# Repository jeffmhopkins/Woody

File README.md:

# Woody

A custom electronic woodwind instrument: a wooden body with mechanical key
switches, breath and motion sensing, driving control voltage into a Eurorack
system.

This is the second iteration of the
[Open Woodwind Project](https://github.com/jeffmhopkins/Open-Woodwind-Project)
(2021), rebuilt from scratch with modern components. The previous version was a
Teensy 3.2 with capacitive touch keys and an onboard synthesizer. This one keeps
almost none of that: mechanical switches instead of capacitive pads, an ESP32-S3
instead of a Teensy, CV output instead of an onboard synth engine.

**Status: Phase 0.** Design decisions are being recorded; no hardware has been
built. Switches and keycaps are purchased. See [ROADMAP.md](ROADMAP.md).

## What it is

The project splits into two physical deliverables that meet over a single cable:

| | **Controller** | **Interface module** |
|---|---|---|
| Form | Laminated wood/aluminium/acrylic body | 10HP Eurorack module |
| Contains | Keys, breath sensor, IMU, LED matrix, MCU | DAC, analog scaling, jacks, knobs |
| Domain | Digital | Analog, ±12V |
| Primary risk | Mechanical and ergonomic | Analog precision |

The controller carries no battery and no output jacks, and all CV **scaling,
conversion and output** happens in the module. It is **not** purely digital —
it holds the pressure sensor, a precision reference, two op-amp stages and the
analog drive onto the umbilical, which is where most of the project's analog
risk lives (ADR 0003). An earlier version of this sentence said otherwise, and
ADR 0004 records that the claim let a review finding through unchallenged.

It takes power from the rack over the umbilical and sends channel data
down the same cable as SPI. The module's analog sits inches from
the jacks it drives.

These two can be developed and tested independently, and the module can be
brought up standalone on a bench long before the instrument exists.

### Output

Six CV channels from the module:

- **Pitch** — dedicated, 1V/oct, −2V to +7V, per-unit calibrated
- **Breath** — dedicated, 0–10V, with panel knobs for gain and offset
- **Mod 1–4** — assignable; source, scale, offset, curve and slew configured
  in the instrument's configuration mode, over Wi-Fi from a phone (ADR 0015,
  *Amendment, 2026-10-04*; the firmware is deferred)

And **MIDI out** on a 3.5 mm TRS jack in the tail cap, beside the etherCON,
Type A or B by a setting (`hardware/carrier/midi-out/`).

## Design scope

**This is a tethered rack instrument.** It is powered by a Eurorack system,
patched into one, and played in front of one. That is the design case, and
decisions get made for it.

It is explicitly **not**: battery powered, wireless in play, standalone, a
MIDI controller product, or a touring instrument. (Its radio is on only in a
configuration mode, for settings and updates, which does not play.) Requirements that only make sense
away from the rack do not belong here, and past versions of these documents
drifted into arguing for some of them.

The external USB is gone (issue #37): the Matrix's own USB-C is a bench and
recovery port, reached with the lid off. The MIDI out replaces USB MIDI as
the way keys, fingering and breath response get validated in a DAW before any
analog hardware is built (milestone E5). It does not get to constrain anything.

There is no onboard synthesizer. There is no battery.

**The target rack has a generous supply and a regulated +5 V rail.** Both are
stated properties of the system this is built for, not assumptions to be
defended. Rack current budget is therefore **not** a design constraint here, and
arguments of the form "a small Eurorack PSU might not cope" do not apply.

That relief is narrower than it sounds, and worth stating precisely so nobody
re-derives the wrong caution later. What still binds:

- **Heat.** The body is oak and acrylic — insulators — and sealed. Every watt
  leaves through the aluminium plate, part of which is under the player's hands.
- **The instrument's own 5 V regulator**, which is a 1 A part at the end of a
  2 m cable, not the rack supply.
- **Fault current**, which a larger supply makes *worse*, not better.

## Licence

Three share-alike licences, one per kind of work — **GPL-3.0-only** for
firmware, **CERN-OHL-S-2.0** for hardware and mechanical design,
**CC-BY-SA-4.0** for documentation. Derivatives stay open on the same terms.

See [`LICENSE`](LICENSE) for the mapping and the reasoning, and
[ADR 0011](docs/decisions/0011-licensing.md) for why it is three rather than
one.

## Repository layout

```
docs/decisions/   Architecture decision records — the important stuff
docs/log/         Dated build log
docs/reference/   Latency budgets, fingering notes, specs
docs/research/    Component comparisons and datasheet notes
docs/review/      Cold review waves. A dated record, never corrected
datasheets/       The actual vendor PDFs, one MANIFEST.csv row each
hardware/         Schematics, split by CIRCUIT under each board:
                    <board>/<circuit>/<circuit>.md  the drawing + derivations
                                      bom.csv       fragment; generates the BOM
                                      circuit.yaml  declared dependencies
                                      notes.md      what it used to be
                  interfaces/  the three circuits that cross a board boundary
                  boards/      one KiCad project per physical board, placing the
                               circuit sheets; the KiCad sheets are the source
                               of truth (ADR 0019, docs/reference/tooling.md)
                  bom.csv      GENERATED from the fragments - do not edit
firmware/         ESP32-S3 firmware (PlatformIO)
mechanical/       Body CAD (OpenSCAD, parametric): renders, DXF cut files and
                  a design-rule report, all GENERATED by tools/cad.py and
                  fingerprinted against their sources - see mechanical/README.md
config/           figures.yaml - THE SHARED-FIGURE REGISTER, the single
                  source of truth for every value used in more than one
                  document; plus key layout and routing, as data
tools/            Host-side utilities
branding/         The Space Coast Synthesizers mark: build.py generates the
                  laser artwork (SVG/DXF), a test print and renders
CLAUDE.md         THE WORKING RULES. Read this before editing anything -
                  it is short, and every rule in it was paid for once
```

*(`docs/review/` and `datasheets/` were missing from this tree until
2026-09-21. `datasheets/` is the largest directory in the repository;
`docs/review/` holds a wave per directory — `ls -d docs/review/*/` is the
count, and there is deliberately no number in this sentence. Both were
invisible in the one file a new reader opens first. The counts that used to
sit here — "77 banked documents", "seven waves", then "nine waves" — were
each true when written and wrong within the week, which is the whole reason
this repository cites rather than
restates.)*

## Where to start reading

1. [ROADMAP.md](ROADMAP.md) — the three tracks and what "done" means for each
2. [hardware/README.md](hardware/README.md) — **how the schematics are
   organised**: one circuit per directory, what the four files in each are,
   and the two rules that will bite you. Start here before opening any
   circuit page.
3. [docs/decisions/](docs/decisions/) — every choice made so far, and why
4. [docs/reference/latency-budget.md](docs/reference/latency-budget.md) — the
   constraint that shapes most of the electrical design
5. [docs/reference/repo-maintenance.md](docs/reference/repo-maintenance.md) —
   which files are generated, which are history, what each tool owns
6. [docs/reference/tooling.md](docs/reference/tooling.md) — **installing and
   using the tools**: the body CAD (OpenSCAD) and the schematic sheets
   (KiCad 9), one setup script for both

*(Entry 2 was missing until 2026-09-21. `hardware/README.md` — the page that
explains the whole `<board>/<circuit>/` scheme the restructure exists to
create — had **zero inbound links from anywhere in the corpus**, so the tree
was navigable by `grep` and by already knowing where things were, which is
the condition the restructure was meant to end.)*

*(This file carried a second "Licensing" section here saying the licence was
"not yet decided", contradicting the "Licence" section above it, which states
the three that were chosen. ADR 0011 has read `Accepted` since it was written
and `LICENSE` has held the mapping the whole time. Deleted 2026-09-21 — the
licence is stated once, above, and nowhere else.)*

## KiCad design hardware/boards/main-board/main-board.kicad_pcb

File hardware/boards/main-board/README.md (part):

# Main board — `main-board`

The one long board at the thumb level (ADR 0017). It carries:
- the thumb switches and both thumb registers;
- the carrier's circuits: the breath sensor's reference, buffer and ADC, power
  entry, the LED drive and the LED row (ADR 0028), the service header and the
  SPI egress;
- the key chain's two ribbon headers;
- `J-UMB`, where the umbilical arrives from the etherCON's adapter (ADR 0021).

The Matrix is on the right-hand key board's rails (ADR 0021 amendment
2026-10-02) and reaches it by an IDC ribbon from that board into `J-MCU`. The board
is part of the cassette (ADR 0025): every one of its mounts stands on the one
bottom plate, and eight of them are columns up to the key boards (ADR 0022 as
amended).

> **Status (2026-11-21): laid out by hand (#48, ADR 0030), the two `J-CHAIN` headers vertical since #49; `pcb.py check` passes.**
> `main_layout.py` places every part and writes out every track and via; no router ran.
> It follows the two key boards and the Matrix carrier: both `J-CHAIN` headers stand
> straight under theirs, and `J-MCU` takes the ribbon's new pin order. The outline, the thirteen
> LEDs, the switches, the mounts and the connectors are where the body CAD puts them
> (`mechanical/export/main-board.dxf`, the `main` entries in
> `mechanical/export/pcb-geometry.echo`). `fab/` and the renders are this board's. The
> sheets are the source and pass KiCad's ERC. Every part has its footprint and bought
> part on its symbol (`Footprint`, `Manufacturer`, `MPN`, `LCSC`, `Assembly`), from
> selections whose datasheets are banked, and every machine-placed part with a polarity
> or more than two pads has its JLC rotation (`hardware/lib/jlc-rotation.csv`). The
> thumb switch positions are provisional until M2/M3, as the key boards' are.

What each circuit does, and why, is on its page:
- [`carrier.md`](../../carrier/carrier.md), the board's own page, and its
  circuits:
  - [`breath-adc`](../../carrier/breath-adc/breath-adc.md)
  - [`breath-excitation-reference`](../../carrier/breath-excitation-reference/breath-excitation-reference.md)
  - [`power-entry-instrument`](../../carrier/power-entry-instrument/power-entry-instrument.md)
  - [`service-uart`](../../carrier/service-uart/service-uart.md)
  - [`led-strip-drive`](../../carrier/led-strip-drive/led-strip-drive.md)
- The thumb clusters:
  - [`key-register`](../../cluster/key-register/key-register.md)
  - [`key-switch-network`](../../cluster/key-switch-network/key-switch-network.md)
  - [`key-marker-and-bits`](../../cluster/key-marker-and-bits/key-marker-and-bits.md)
- The interfaces whose main-board parts the root sheet draws:
  - [`key-chain-loom`](../../interfaces/key-chain-loom/key-chain-loom.md)
  - [`breath-sense-link`](../../interfaces/breath-sense-link/breath-sense-link.md)
  - [`spi-link`](../../interfaces/spi-link/spi-link.md)

## Files — what is source, what is generated

| File | What it is |
|---|---|
| `main-board.kicad_sch` (+ the circuit sheets it places) | **Source.** Every connection, and each part's identity (ADR 0019) |
| `board-netlist.yaml` | Exported from the sheets (`tools/kicad.py export hardware/boards/main-board`), with KiCad's ERC over the whole hierarchy |
| `*.sch.png`, `*.pcb-*.png` | Renders, recorded in `hardware/SHEETS.csv` |
| `fab/` | **Generated** by `tools/pcb.py render` (Gerbers, drill, placement), recorded in the ledger against the board and the sheets. Never edit it by hand: `kicad.py check` fails on a stale file, and on any file in `fab/` that no tool wrote |
| `fp-lib-table` | Registers `hardware/lib/woody.pretty` (the KS-33, `J-CHAIN`, `J-MCU`, `J-UMB`, MPXV4006DP and WS2815B-V1 footprints, and through them their 3D models) for this project |
| `sym-lib-table` | Registers `hardware/lib/woody.kicad_sym` (the WS2815B-V1's symbol) for this project |
| `main_layout.py` | **The record of the layout** (ADR 0030): every part's place and every track and via, written out by hand with the reason for each. It rewrites `main-board.kicad_pcb`. No router runs on this board |
| `main-board.kicad_pcb`, `main-board.kicad_pro` | Written by `main_layout.py`. Change the layout there and run it, so the reasons stay with the copper; `pcb.py check` holds the board to the sheets, the body CAD and `layout.yaml` |
| `layout.yaml` | The limits the board is held to (`kind: main`): the rules, the stackup, the planes, the `AGND_INST` island and its tie, the breath pair's keep-off, the net classes, keep-outs, heights, iron room, and what its silkscreen says |

The root sheet places, once per instance:
- **the six carrier circuits**;
- **`breath-sense-link`**, whose parts are all on this board;
- **the two thumb registers** (`REG-LT`, `REG-RT`);
- **one key network per thumb key**, plus one at each of the right thumb's
  two reserved spare positions (`sw+`, `sw-`);
- **one pull-up per free bit** (`FREE1`, `FREE2`).

The registers' inputs are wired as `hardware/cluster/key-marker-and-bits/allocation.yaml`
says. Its own parts are the interface circuits' main-board halves:
- from key-chain-loom: both `J-CHAIN` headers, the series resistors, the
  SER terminator, the two beads and the clamp;
- from spi-link: `J-UMB`.

On this board the chain's return is `PWR_GND` and its 3V3 is `DEV_3V3`
(`hardware/nets.yaml`).

`tools/kicad.py check` holds the board to three things:
- the registers' wiring against `allocation.yaml`;
- each `J-CHAIN` pin against the loom's `J-CHAIN-MAIN-<LH|RH>`;
- ERC.

## The references

Numeric, as the key boards'. The BOM row each one buys from is its `Row` field.

| References | BOM row | Sheet |
|---|---|---|
| C1 | `C-AA-ADC` | breath-adc |
| C2 | `C-ADC-BULK` | breath-adc |
| C42 | `C-ADC-VDD` | breath-adc |
| C11 | `C-BUCK-IN` | power-entry-instrument |
| C43 | `C-BUCK-OUT` | power-entry-instrument |
| C13, C14, C205, C206 | `C-DECOUPLE-165` | REG-LT, REG-RT |
| C3, C6–C8, C12, C204 | `C-DECOUPLE-CARRIER` | breath-adc, breath-excitation-reference, led-strip-drive |
| C9 | `C-FB-REF` | breath-excitation-reference |
| C40 | `C-INRUSH-GD` | power-entry-instrument |
| C39 | `C-INRUSH-GS` | power-entry-instrument |
| C15–C24 | `C-KEY` | LT1, LT2, LT3, LT4, RT1, RT2, RT3, RT4, sw+, sw- |
| C26–C38 | `C-LED` | led-strip-drive |
| C4, C5 | `C-REF-OUT` | breath-excitation-reference |
| C203 | `C-SENSOR-OUT` | breath-sense-link |
| C201 | `C-SENSOR-VS-BULK` | breath-sense-link |
| C202 | `C-SENSOR-VS-HF` | breath-sense-link |
| C10, C44 | `C-STRIP-BULK` | power-entry-instrument |
| C45–C47 | `C-STITCH-12V` | power-entry-instrument |
| C207, C208 | `C-USBOR` | power-entry-instrument (#39) |
| D21 | `D-INRUSH-RST` | power-entry-instrument |
| D8–D20 | `D-LED` | led-strip-drive |
| D1 | `D-REF-CLAMP` | breath-excitation-reference |
| D2 | `D-REVSHUNT` | power-entry-instrument |
| D5, D6 | `D-TVS-BREATH` | breath-sense-link |
| D3 | `D-TVS-PWR` | power-entry-instrument |
| FB1, FB2 | `FB-CHAIN` | root |
| FB3, FB4 | `FB-MIDI` | midi-out (#37) |
| J2 | `HDR-SERVICE` | service-uart |
| J4, J5 | `J-CHAIN` | root |
| J7 | `J-MIDI` | midi-out (#37; side entry facing the tail since #45) |
| J8 | `J-MIDI-OUT` | midi-out (#37; through the tail cap since #45, not on this board: `layout.yaml` `not_on_board:`) |
| J1 | `J-MCU` | carrier |
| J6 | `J-UMB` | root |
| L1 | `L-BUCK-IN` | power-entry-instrument |
| NT2 | `NT-AGND` | power-entry-instrument |
| NT1 | `NT-DIG` | carrier |
| Q1 | `Q-INRUSH` | power-entry-instrument |
| Q2 | `Q-USBOR` | power-entry-instrument (#39) |
| R54, R55 | `R-ADC-SER` | breath-adc |
| R47 | `R-ADC-VDD` | breath-adc |
| R5 | `R-ADCDIV-L` | breath-adc |
| R4 | `R-ADCDIV-U` | breath-adc |
| R34–R36 | `R-CHAIN-SER` | root |
| R45 | `R-CS-PULL-ADC` | breath-adc |
| R40 | `R-CS-PULL-INST` | carrier |
| R8 | `R-FB-REF` | breath-excitation-reference |
| R9 | `R-FBX-REF` | breath-excitation-reference |
| R44 | `R-HOP-SER` | root |
| R52, R53 | `R-HOP-SER` | root |
| R42 | `R-INRUSH-G` | power-entry-instrument |
| R43 | `R-INRUSH-GD` | power-entry-instrument |
| R41 | `R-INRUSH-GS` | power-entry-instrument |
| R7 | `R-ISO-REF` | breath-excitation-reference |
| R12, R14, R16, R18, R20, R22, R24, R26, R28, R30, R32, R33 | `R-KEY-PU` | LT1, LT2, LT3, LT4, RT1, RT2, RT3, RT4, sw+, sw-, FREE1, FREE2 |
| R13, R15, R17, R19, R21, R23, R25, R27, R29, R31 | `R-KEY-SER` | LT1, LT2, LT3, LT4, RT1, RT2, RT3, RT4, sw+, sw- |
| R10 | `R-LED-PD` | led-strip-drive |
| R50, R51 | `R-MIDI` | midi-out (#37) |
| R48, R49 | `R-MIDI-PU` | led-strip-drive (#37) |
| R11 | `R-LED-SER` | led-strip-drive |
| R6 | `R-REF-IN` | breath-excitation-reference |
| R38, R39 | `R-SER-BREATH-INST` | breath-sense-link |
| R37 | `R-SER-TERM` | root |
| R1–R3 | `R-SPI-SER` | carrier |
| R56 | `R-RXD-SER` | service-uart |
| R46 | `R-TXD-SER` | service-uart |
| SW1–SW10 | `SW1-n` | LT1, LT2, LT3, LT4, RT1, RT2, RT3, RT4, sw+, sw- |
| U2 | `U-ADC` | breath-adc |
| U10 | `U-BREATH` | breath-sense-link |
| U5 | `U-BUCK` | power-entry-instrument |
| U3 | `U-BUF` | breath-excitation-reference |
| U7, U8 | `U-KEYS` | REG-LT, REG-RT |
| U6 | `U-LVLSHIFT` | led-strip-drive |
| A1 | `U-MCU-RT` | carrier |
| U4 | `U-REF-BREATH` | breath-excitation-reference |
| U9, U11 | `U-TVS-CHAIN` | root |
| U12 | `U-TVS-MIDI` | midi-out (#37) |
| U1 | `U-TVS-SPI` | carrier |
| U13 | `U-USBOR` | power-entry-instrument (#39) |

## Open, and what decides each

What is still open:

| Item | Decided by |
|---|---|
| **The LED row's places** are the body CAD's (`pcb-geometry.echo` `main` `led`, *"LED row on the main board"* in `mechanical/drc.echo`): thirteen LEDs on the centreline, `D8` (LED 1, first on the data line) past the Matrix ribbon and `D9` before it, the same distance from its edge, and `D9` to `D20` at one pitch to the mouth end (`lighting.led_tail_x`, `led_ribbon_x`, `led_pitch`; ADR 0028's amendment of 2026-11-21, whose point 2 is the LED that stands level with `J5`) (`D7` / `C25` went with the removed LED); each `C-LED` in the row on the mouth side of its LED, but `D8`'s beyond `D3`, which stands in the row between them, and `D20`'s on its far side, off the breath sensor (`main_layout.py`). Reshuffled if the diffusion test moves the count. **The WS2815B-V1's chamfer marks pin 1 (NC)**; the footprint's silk triangle marks the chamfer, and JLCPCB's own footprint agrees (`hardware/lib/README.md`) | Layout; the side-light diffusion test; the first order's placement preview |
| **Passives may go on the underside** (owner, 2026-09-29). The underside faces the grounded bottom plate, `hardware.kb_spacer_l` below it, over the board's whole length since the cassette (ADR 0025). At `boards.board_clear` that leaves no room for a part (`mechanical/drc.echo` *"main board underside room over the bottom plate"*), so an underside part needs a **window cut through the bottom plate** under it, down to the oak (the second figure on that line), and must be clear of the thumb switches' housings, pins and the mounts' spacers. Through-hole tails face the plate too: the next row. The thumb switches are already underside parts | The layout; each window goes into the bottom plate's outline in the body CAD |
| **Through-hole tails under the board** (2026-10-01): every part with plated through-hole pins pokes its tails out of the underside toward the grounded bottom plate — `J-CHAIN` ×2, `J-MCU`, `J-UMB` and `U-BUCK` (`config/body.yaml`, *THE THROUGH-HOLE TAILS UNDER THE MAIN BOARD*, says which and why these). `mechanical/drc.echo` *"through-hole tails under the main board clear of the bottom plate"* tests each against what is under it, and the body model draws them for `clash.txt`. `J-CHAIN`'s and `J-MCU`'s clear the plate as supplied. The plate ends short of `J-UMB`'s tail row, and has a window to the oak under the regulator block (`HDR-SERVICE` is surface mount since 2026-10-06, owner, and needs none) (`pcb-geometry.echo` `main` `plate`). **`U-BUCK`'s pins are cut to `boards.tht_trim` below the board after soldering** — as supplied they reach the oak even through the window. `U-BUCK` stands inside the regulator block, or the window moves with it | A part moved off its window: move the block and rebuild the body CAD; a new through-hole part: add it to `tht_tails` in `mechanical/cad/woody_body.scad` |
| **The references with no clear place on the silkscreen** stay on the fabrication layer. `tools/pcb_silk.py` (#54) places every one that has a clear place within reach of its part, on a leader line where the place is not beside it; `python3 tools/pcb_silk.py hardware/boards/main-board --audit` lists the ones left, which stand in the tightest groups (the inrush corner at the tail, the far-edge rows over the key registers) | **Decided** (owner, 2026-11-22, #54): they stay off the silkscreen, on the fab layer's assembly drawing only; no part moves for a label |
| **`C203` at `U10` pin 4** (MPXV4006DP Fig. 3): pin 4 is the corner of `U10`'s own courtyard, at the mouth and far edges, so no 0805 can stand within 3 mm of it on the top face; `C203` stands at `U3`'s input, the net's other end, as before. Nearer needs an underside part and a bottom-plate window under it | Owner |
| **`J-CHAIN` ×2 and `J-MCU` (and `J-MCU-C` on the Matrix carrier, the same footprint): their pads**' ring is at JLC's absolute minimum on the sides facing a neighbour (`fab: annular_min`; pre-fab review, issue #52 F6). It stays: the hole is the one the header's drawing asks for (`datasheets/connectors/CNCTECH-3220-XX-0100-00-1.27MM-BOX-HEADER-VERTICAL.pdf`, *Recommended PCB layout*), a smaller one gives the ring a few hundredths and takes them from the post's fit, and the pitch leaves the pad no room to grow that way (`hardware/lib/README.md`, the IDC header's row). Ask JLC's review of the production file to accept the thin side | The first order |
| **The umbilical adapter** (`PCB-UMB-ADAPTER`) is a separate small board: its schematic is [`../umb-adapter/`](../umb-adapter/README.md), not laid out | With this board's layout |

What the layout holds, and where:
- **Four layers** (ADR 0017 amendment 2026-09-29), JLCPCB's stack
  `JLC04161H-7628` [ds `datasheets/fab/JLCPCB-IMPEDANCE-STACKUPS.pdf`]. Layer 2 `PWR_GND`, layer 3
  the +12 V behind `Q-INRUSH` (`INST_POS12`, `power-entry-instrument.md` §1a); the +12 V
  ahead of it and the other rails are tracks (`layout.yaml` `net_classes:`). **`AGND_INST` is an island on layer 2** round the analog block,
  its moat bridged once by `NT-AGND` (NT2) on `U-ADC`'s tail side, where its digital pins
  (5-7) cross the moat inside the tie's window (`power-entry-instrument.md` §2); since wave 3
  the island takes all of `U-ADC` and the pocket above it where `ADC_VDD`'s capacitors
  stand (#8-3). `check` fails a second tie, an island pad off the island, and any layer-1
  track crossing the moat but at the tie or as the breath pair.
- **White solder mask** both faces, black legend (`layout.yaml` `fab:`; ADR 0028).
- **Every mount plated on `PWR_GND`**, pads both faces, no other net's copper under
  its hardware (`check`); the U-bolt legs' holes unplated, the outer layers kept
  clear round their hardware.
- **The regulator block holds `U-BUCK` alone** (a rule area), against the near edge
  (`boards.tall_side`; the far edge carries the breath pair), `C-STRIP-BULK`,
  `C-BUCK-IN` and `L-BUCK-IN` beside it where their heights fit (`check_heights`).
- **`A1` (the Matrix) and the spare switches `SW9`, `SW10`** are on the sheets and
  not on this board (`layout.yaml` `not_on_board:`, reported as notes); the spare
  positions' networks are placed.
- **`NT1`** at `J-UMB` pin 8 (ADR 0018); **`U-TVS-SPI`** on the J-MCU side of
  `R-SPI-SER`, where its three channels now are.
- **The thumb switches on the underside**, where the body CAD puts them, the near
  row turned 180° (ADR 0022).
- **`U-BREATH`'s ports point to the tail**, as the body CAD and
  `breath-sense-link.md` (*Mounting*) put them, which turns its pins 1–4 (`VS`,
  `GND`, `Vout`) to the board's far edge, away from the rest of the analog block;
  the island reaches round them (`layout.yaml` `cad_parts:`, `islands:`).
- **Every part's place and every track and via are `main_layout.py`'s** (ADR 0030). Its
  header gives the floorplan and why each part stands where it does; each stage's
  function gives its lines in the order the signal runs. In outline:
  - **The analog block** is laid out along its signal from the sensor's pins outward, on
    layer 1 over the island. The ADC's chip select and 3V3 arrive on the bottom face and
    come up inside the island, so only its three SPI lines cross the island's edge,
    beside `NT-AGND`.
  - **The breath pair** (owner, 2026-10-03: *"the analog path should just be routed along
    the top"*, the far edge): the buffer's output and its `AGND` leg side by side on
    layer 4 from the buffer along the far edge to `R38` / `R39` at `J-UMB`, stepping
    inboard at 45 degrees under each far column mount. The `AGND` leg is the inboard
    line, between the signal and every key. Its reference is the `AGND_INST` strip cut
    out of layer 3 under it. Every other net's copper on that layer, and every via,
    keeps 3W off it (`layout.yaml` `pairs:` `guard:`, held by `pcb.py check`). It has no
    guard tracks: nothing else runs in that band on that layer.
  - **The LED data line stays on the top face** from the second LED to the mouth end.
    The first LED stands beyond the driver, in the row's tail-end place, so its two
    lines (`LED_DI` to it, `LED_D1` back from it) each take a lane on the bottom face
    under the driver: two vias a line. Each LED's capacitor stands in the row beside
    it, and their supply and ground pads reach the planes by vias beside them.
  - **The bottom face carries the lines that run the board's length**: the chain's
    trunk north of the LED row, the ADC's four lines and its 3V3 south of it, and each
    near-row key's line where it crosses under the row.
  - **The power paths carry no via** (#8-6): `UMBILICAL_POS12`, `BUCK_IN`, `BUCK_A_OUT`
    and `INST_5V_A` to the 5 V OR are top-face tracks from end to end. Where a power
    part meets a plane it does so by more than one via: three at `Q-INRUSH`'s drain, two
    at each bulk capacitor's pad, the buck's capacitors' returns, `L-BUCK-IN` and
    `D-TVS-PWR`. `D-REVSHUNT`'s anode is a track to `J-UMB`'s own ground pin.
  - **Ground**: every surface pad on `PWR_GND` has a via beside it, or shares one with
    the pad facing it. None stands in a pad (ADR 0030, point 5): the three clamps' middle
    pins, `U9` pin 2, `U11` pin 2 and `U1` pin 2, have theirs just off the pad, the line
    that passed there stepped clear of it.
- **Soldered ground pins meet the plane through relief spokes**, as on the key boards.
  `J-MCU`'s ground pins have one spoke each, all a 1.27 mm header leaves room for;
  `main-board.kicad_dru` lets those pins pass with one where the board's rule asks two
  (ADR 0030, Amendment of 2026-11-22). The one exception is the mounts, which join the
  plane solid: they are clamped and never soldered.
- **The clamps at their connector** (#8-9): `D-REVSHUNT` (D2) beside `J-UMB`'s pins 3 and
  6, and `D-TVS-PWR` (D3) on a top-face track from D2's pad, in the LED row on the mouth
  side of the first LED since that LED took the tail-end place; the buck's capacitors at
  the module (#8-7).
- **Soldering-iron room round the hand-soldered pads** (#34; `layout.yaml` `iron_room:`,
  held by `pcb.py check`): every other part's courtyard 2.0 mm from a thumb switch's pin
  pads on the top face, where they are soldered, and 1.5 mm from `U10`'s. This layout
  meets it everywhere, with no exception listed.
- **The planes stitched** (#8-8; owner, 2026-10-04, in the working chat: *"add 2-3 now"*):
  `C-STITCH-12V` from `INST_POS12` to `PWR_GND` at `J-MCU` (`C45`), `J-UMB` (`C46`) and the
  analog end (`C47`, on `PWR_GND` beside the island), each pad to its plane by its own via
  (`power-entry-instrument.md` §2, *Plane stitching*).

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
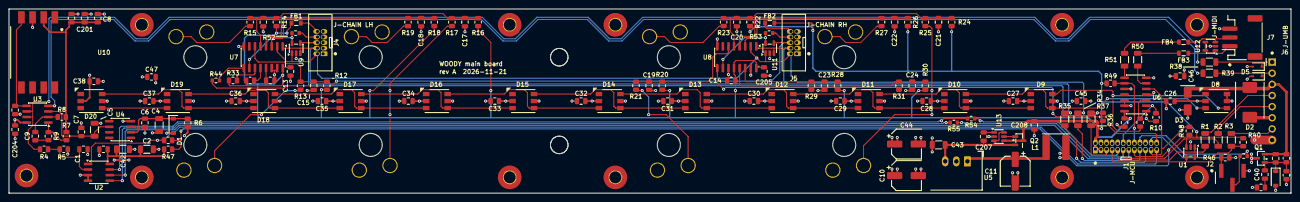
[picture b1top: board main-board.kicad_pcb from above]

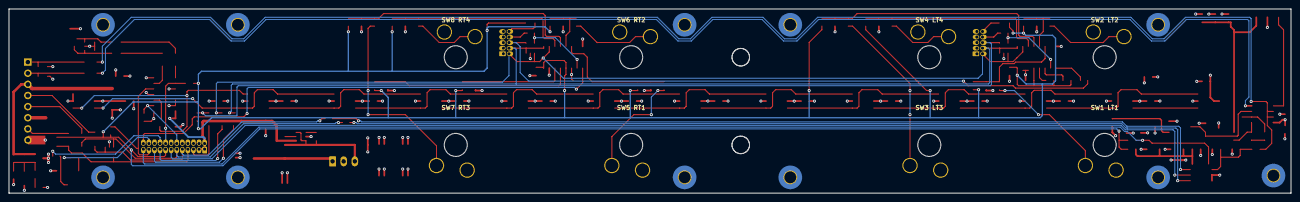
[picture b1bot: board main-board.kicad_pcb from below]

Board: 4 copper layers, 292.4 x 42.0 mm, 175 parts (8 on the bottom side), 97 nets.

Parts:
C1: 18nF C0G/NP0; C_0805_2012Metric
C2, C4, C5, C43: 10uF; C_1206_3216Metric
C3, C6, C7, C8, C12, C13, C14, C26, C27, C28, C29, C30, C31, C32, C33, C34, C35, C36, C37, C38, C204, C205, C206: 100nF; C_0805_2012Metric
C9: 1nF; C_0805_2012Metric
C10, C44: 220uF 25V; CP_Elec_6.3x7.7
C11: 100uF; CP_Elec_6.3x5.8
C15, C16, C17, C18, C19, C20, C21, C22, C23, C24: 47nF; C_0805_2012Metric
C39: 1uF 50V X7R; C_0805_2012Metric
C40: 22nF 50V X7R; C_0805_2012Metric
C42: 22uF; C_1206_3216Metric
C45, C46, C47, C207, C208: 100nF 50V X7R; C_0805_2012Metric
C201: 1uF; C_0805_2012Metric
C202: 10nF; C_0805_2012Metric
C203: 470pF; C_0805_2012Metric
D1: 15V zener; D_SOD-123
D2: SS34; D_SMC
D3: SMAJ15A; D_SMA
D5, D6: PESD12VL1BA; D_SOD-323
D8, D9, D10, D11, D12, D13, D14, D15, D16, D17, D18, D19, D20: WS2815B-V1; LED_WS2815B-V1_PLCC6_5.4x5.0mm_P1.6mm
D21: 1N4148W; D_SOD-123
FB1, FB2: Ferrite bead 600R @ 100MHz; L_0805_2012Metric
FB3, FB4: 600R@100MHz; L_0805_2012Metric
H1, H2, H3, H4, H5, H6, H7, H8: mount column; MountingHole_2.7mm_M2.5_Pad_TopBottom
H9, H10, H11: mount end; MountingHole_2.7mm_M2.5_Pad_TopBottom
J1: 2x12 1.27mm shrouded box header; IDC-Header_2x12_P1.27mm_Vertical
J2: 1x3; PinHeader_1x03_P2.54mm_Vertical_SMD_Hanxia_PZ2.54-TP-YQ
J4, J5: 10-way; IDC-Header_2x05_P1.27mm_CNCTech_3220_Vertical
J6: 8-way 2.54mm right-angle pin header; PinHeader_1x08_P2.54mm_Horizontal_Hanxia_PZ2.54-WZ
J7: S3B-PH-SM4-TB; JST_PH_S3B-PH-SM4-TB_1x03-1MP_P2.00mm_Horizontal
L1: 22uH; L_Sunlord_SWPA6028S
NT1: net tie; NetTie-2_SMD_Pad2.0mm
NT2: net tie; NetTie-2_SMD_Pad0.5mm
Q1: AO3401A; SOT-23
Q2: DMN3404L; SOT-23
R1, R2, R3: 82R 1%; R_1206_3216Metric
R4, R8, R10, R40, R45, R48, R49: 10k 1%; R_0805_2012Metric
R5: 15k 1%; R_0805_2012Metric
R6: 330R 1%; R_0805_2012Metric
R7: 37.4R 1%; R_0805_2012Metric
R9, R13, R15, R17, R19, R21, R23, R25, R27, R29, R31: 100R 1%; R_0805_2012Metric
R11: 330R; R_0805_2012Metric
R12, R14, R16, R18, R20, R22, R24, R26, R28, R30, R32, R33: 2k2 1%; R_0805_2012Metric
R34, R35, R36: 100R 1%; R_1206_3216Metric
R37: 10k; R_0805_2012Metric
R38, R39: 1k 1%; R_1206_3216Metric
R41, R42: 1M 1%; R_0805_2012Metric
R43: 22R 1%; R_0805_2012Metric
R44, R52, R53: 2k2 1%; R_0603_1608Metric
R46: 499R 1%; R_0805_2012Metric
R47: 10R 1%; R_0805_2012Metric
R50, R51: 182R 1%; R_1206_3216Metric
R54, R55: 47R 1%; R_0603_1608Metric
R56: 1k 1%; R_0603_1608Metric
SW1, SW2, SW3, SW4, SW5, SW6, SW7, SW8: KS-33; SW_Gateron_KS33_1u
U1: SP0504BAHT or equivalent 4-channel 5V array; SOT-23-5
U2: MCP3202-CI/SN; SOIC-8_3.9x4.9mm_P1.27mm
U3: OPA2197IDR; SOIC-8_3.9x4.9mm_P1.27mm
U4: REF5050IDR; SOIC-8_3.9x4.9mm_P1.27mm
U5: R-78E5.0-1.0; Converter_DCDC_RECOM_R-78E-0.5_THT
U6: 74AHCT125; SOIC-14_3.9x8.7mm_P1.27mm
U7, U8: 74HCS165; SOIC-16_3.9x9.9mm_P1.27mm
U9, U11: SP0504BAHTG 4-channel 5V array; SOT-23-5
U10: MPXV4006DP; NXP_Case1351-01_SOP-8_P2.54mm
U12: SP0504BAHTG; SOT-23-5
U13: LM74700-Q1; SOT-23-6

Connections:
/AGND_SENSE: D6.1, J6.2, R39.2
/BREATH_SENSE: D5.1, J6.1, R38.2
/CHAIN_QH_RT: J1.24, U8.9
/CHAIN_SCK: J4.2, J5.2, R34.2, U7.2, U8.2, U9.1, U11.1
/CHAIN_SER_LH: J4.6, R36.2, R37.1, U9.4
/CHAIN_SHLD: J4.4, J5.4, R35.2, U7.1, U8.1, U9.3, U11.3
/CS_MOD: J6.7, R3.2
/DIG_GND: J6.8, NT1.1
/HOP_LH_LT: J4.8, R52.1
/HOP_LT_QH: R44.1, U7.9
/HOP_LT_RH: J5.6, R44.2, U11.4
/HOP_LT_SER: R52.2, U7.10, U9.5
/HOP_RH_RT: J5.8, R53.1
/HOP_RT_SER: R53.2, U8.10, U11.5
/IO1: J1.12, R10.1, U6.2
/IO2: J1.16, R49.2, U6.9
/IO6: J1.21, R48.2, U6.5
/IO7: J1.19, R35.1
/IO33: J1.5, R36.1
/IO35: J1.9, R1.1, R54.1, U1.1
/IO36: J1.11, R2.1, R55.1, U1.3
/IO37: J1.13, U2.6
/IO38: J1.17, R34.1
/IO39: J1.23, R45.2, U2.1
/KEY_FREE1: R32.2, U7.12
/KEY_FREE2: R33.2, U7.11
/KEY_LT1: C15.1, R12.2, R13.1, U7.6
/KEY_LT2: C16.1, R14.2, R15.1, U7.5
/KEY_LT3: C17.1, R16.2, R17.1, U7.4
/KEY_LT4: C18.1, R18.2, R19.1, U7.3
/KEY_RT1: C19.1, R20.2, R21.1, U8.6
/KEY_RT2: C20.1, R22.2, R23.1, U8.5
/KEY_RT3: C21.1, R24.2, R25.1, U8.4
/KEY_RT4: C22.1, R26.2, R27.1, U8.3
/KEY_SWM: C24.1, R30.2, R31.1, U8.13
/KEY_SWP: C23.1, R28.2, R29.1, U8.14
/LT1/SWITCH_LEG: R13.2, SW1.1
/LT2/SWITCH_LEG: R15.2, SW2.1
/LT3/SWITCH_LEG: R17.2, SW3.1
/LT4/SWITCH_LEG: R19.2, SW4.1
/MIDI_RING_DRV: R51.1, U6.8
/MIDI_TIP_DRV: R50.1, U6.6
/MOSI: J6.5, R2.2
/RT1/SWITCH_LEG: R21.2, SW5.1
/RT2/SWITCH_LEG: R23.2, SW6.1
/RT3/SWITCH_LEG: R25.2, SW7.1
/RT4/SWITCH_LEG: R27.2, SW8.1
/SCLK: J6.4, R1.2
/SENSOR_BUFFERED_OUT: R4.1, R38.1, U3.6, U3.7
/SENSOR_RAW: C203.1, U3.5, U10.4
/U0RXD: J1.18, R56.1
/U0TXD: J1.22, R46.1
/V3V3_CHAIN_LH: FB1.2, J4.10
/V3V3_CHAIN_RH: FB2.2, J5.10
/breath-adc/ADC_CLK: R54.2, U2.7
/breath-adc/ADC_DIN: R55.2, U2.5
/breath-adc/ADC_IN: C1.1, R4.2, R5.1, U2.2
/breath-adc/ADC_VDD: C2.1, C3.1, C42.1, R47.2, U2.8
/breath-excitation-reference/AC_FB_MID: C9.2, R9.2
/breath-excitation-reference/BUF_OUT: R7.1, R9.1, U3.1
/breath-excitation-reference/REF_5V: C5.1, C7.1, U3.3, U4.6
/breath-excitation-reference/REF_MINUS: C9.1, R8.2, U3.2
/carrier/IO34: J1.7, R3.1, R40.2, U1.4
/led-strip-drive/GATE_A_OUT: R11.1, U6.3
/led-strip-drive/LED_D1: D8.3, D9.4, D10.6
/led-strip-drive/LED_D2: D9.3, D10.4, D11.6
/led-strip-drive/LED_D3: D10.3, D11.4, D12.6
/led-strip-drive/LED_D4: D11.3, D12.4, D13.6
/led-strip-drive/LED_D5: D12.3, D13.4, D14.6
/led-strip-drive/LED_D6: D13.3, D14.4, D15.6
/led-strip-drive/LED_D7: D14.3, D15.4, D16.6
/led-strip-drive/LED_D8: D15.3, D16.4, D17.6
/led-strip-drive/LED_D9: D16.3, D17.4, D18.6
/led-strip-drive/LED_D10: D17.3, D18.4, D19.6
/led-strip-drive/LED_D11: D18.3, D19.4, D20.6
/led-strip-drive/LED_D12: D19.3, D20.4
/led-strip-drive/LED_DI: D8.4, D9.6, R11.2
/midi-out/MIDI_RING: FB4.2, J7.2, U12.3
/midi-out/MIDI_RING_R: FB4.1, R51.2
/midi-out/MIDI_TIP: FB3.2, J7.1, U12.1
/midi-out/MIDI_TIP_R: FB3.1, R50.2
/power-entry-instrument/BUCK_A_OUT: C43.1, C207.2, Q2.2, U5.3, U13.3, U13.6
/power-entry-instrument/INRUSH_GATE: C39.2, C40.1, D21.1, Q1.1, R41.2, R42.1
/power-entry-instrument/INRUSH_MILLER: C40.2, R43.1
/power-entry-instrument/USBOR_GATE: Q2.1, U13.5
/power-entry-instrument/USBOR_VCAP: C207.1, U13.1
/service-uart/RXD_HDR: J2.2, R56.2
/service-uart/TXD_HDR: J2.1, R46.2
AGND_INST: C1.2, C2.2, C3.2, C4.2, C5.2, C6.2, C7.2, C8.2, C42.2, C201.2, C202.2, C203.2, C204.2, D1.2, NT2.1, R5.2, R39.1, U2.3, U2.4, U3.4, U4.4, U10.3
BUCK_IN: C11.1, L1.2, U5.1
DEV_3V3: C13.1, C14.1, C205.1, C206.1, FB1.1, FB2.1, J1.15, R12.1, R14.1, R16.1, R18.1, R20.1, R22.1, R24.1, R26.1, R28.1, R30.1, R32.1, R33.1, R37.2, R40.1, R45.1, R47.1, R48.1, R49.1, U7.13, U7.16, U8.12, U8.16
INST_5V_A: C12.1, C208.1, J1.1, J1.2, J1.3, Q2.3, U6.14, U13.4
INST_POS12: C10.1, C26.1, C27.1, C28.1, C29.1, C30.1, C31.1, C32.1, C33.1, C34.1, C35.1, C36.1, C37.1, C38.1, C44.1, C45.1, C46.1, C47.1, C204.1, D8.2, D9.2, D10.2, D11.2, D12.2, D13.2, D14.2, D15.2, D16.2, D17.2, D18.2, D19.2, D20.2, L1.1, Q1.3, R6.1, R43.2, U3.8
PWR_GND: C10.2, C11.2, C12.2, C13.2, C14.2, C15.2, C16.2, C17.2, C18.2, C19.2, C20.2, C21.2, C22.2, C23.2, C24.2, C26.2, C27.2, C28.2, C29.2, C30.2, C31.2, C32.2, C33.2, C34.2, C35.2, C36.2, C37.2, C38.2, C43.2, C44.2, C45.2, C46.2, C47.2, C205.2, C206.2, C208.2, D2.2, D3.2, D5.2, D6.2, D8.5, D8.6, D9.5, D10.5, D11.5, D12.5, D13.5, D14.5, D15.5, D16.5, D17.5, D18.5, D19.5, D20.5, D21.2, H1.1, H2.1, H3.1, H4.1, H5.1, H6.1, H7.1, H8.1, H9.1, H10.1, H11.1, J1.4, J1.6, J1.8, J1.14, J1.20, J2.3, J4.1, J4.3, J4.5, J4.7, J4.9, J5.1, J5.3, J5.5, J5.7, J5.9, J6.6, J7.3, NT1.2, NT2.2, R10.2, R42.2, SW1.2, SW2.2, SW3.2, SW4.2, SW5.2, SW6.2, SW7.2, SW8.2, U1.2, U5.2, U6.1, U6.4, U6.7, U6.10, U6.12, U6.13, U7.8, U7.14, U7.15, U8.8, U8.11, U8.15, U9.2, U11.2, U12.2, U12.4, U12.5, U13.2
REF_VIN: C4.1, C6.1, D1.1, R6.2, U4.2
UMBILICAL_POS12: C39.1, D2.1, D3.1, J6.3, Q1.2, R41.1
VS: C8.1, C201.1, C202.1, R7.2, R8.1, U10.2

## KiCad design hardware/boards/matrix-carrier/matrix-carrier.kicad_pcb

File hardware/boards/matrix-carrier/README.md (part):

# Matrix carrier — `matrix-carrier`

The board the ESP32-S3-Matrix stands on, hung from the oak top on three
mounts (owner, 2026-10-03: a "SEPARATE SMALL MATRIX CARRIER", "Hang from the
lid", and option A for its outline;
[ADR 0021](../../../docs/decisions/0021-pcb-mount-ethercon.md), *Amendment,
2026-10-03*). It carries nothing but connections: two 1×10 headers under the
Matrix's pad rows, and `J-MCU-C`, a vertical header hung mouth down under its arm, beside the
main board's `J-MCU`, which the Matrix ribbon (`CBL-MCU-RIBBON`) joins.

> **Status: laid out and checked against the main board's `J-MCU`
> (`tools/kicad.py check`); not yet ordered.** Two things are decided with parts in
> hand, before it is ordered (ADR 0021's *Open* table): which side the
> Matrix's 5V..IO1 pad row is on with its USB-C toward the mouth, and the
> recovery plug's overmould (`openings.usb_ext_overmold_w`; the tail-face
> extension it was drawn for is gone since issue #37).

## Where everything comes from

| What | Source |
|---|---|
| The outline (the arm, the USB-C shell's slot), the headers' rows, J-MCU-C's place, the mounts | the body CAD: `mechanical/export/matrix-carrier.dxf`, `pcb-geometry.echo` cluster `matrix` |
| Every connection and each part's identity | `matrix-carrier.kicad_sch` (ADR 0019); `board-netlist.yaml` is exported from it |
| The pin map | **This board sets the ribbon's pin order** (*The ribbon's pins* below); `J-MCU` pin *k* is J-MCU-C pin *k* (the header is turned half a turn; ADR 0018, *Amendment, 2026-11-22*). Each header pin is the Matrix pad it is named for. `tools/kicad.py check` holds both to `hardware/carrier/netlist.yaml` and the header order to the banked Waveshare pin file |
| The layout | `layout.yaml` holds the limits and the fixed parts; **every track is written out in `carrier_layout.py`**, which re-makes the board's copper and says why each line is where it is. No router runs on this board ([ADR 0030](../../../docs/decisions/0030-boards-laid-out-by-hand.md), *Amendment, 2026-11-20*) |

## How this board is laid out

- **Every line is on the top face**, where the Matrix's two pad rows are
  soldered. The top face has no pour.
- **The bottom face is one whole ground plane.** The board's one via takes the
  Matrix's ground pad down to it.
- **No line crosses another**, because the ribbon's pins are in the order the
  lines arrive in. J-MCU-C's front row leaves toward the far pad row and its
  back row toward the near one, each pin on a lane of its own.
- **Three lines neck to the layout's `track_min`** where they pass together
  between two feet of the near pad row. It is the only neck on the board.
- **J-MCU-C's ground pins meet the plane through one relief spoke each**:
  the neighbouring pads leave room for one only, and `matrix-carrier.kicad_dru`
  lets those pins pass with one where the board's rule asks two (ADR 0030,
  Amendment of 2026-11-22). The mounts join the plane solid, being bolted.

## The ribbon's pins

J-MCU-C (`J1`). The order along the header is the owner's choice of
2026-11-20 ("Re-order the ribbon pins"); the numbers are those of a header
turned half a turn (owner, 2026-11-22), so each is `J-MCU`'s pin of the same
number and the ribbon is a bought one, made pin 1 to pin 1 (`CBL-MCU-RIBBON`).
The odd pins are the front row, toward the far side; column 1 is the one
nearest the Matrix. Pin 6 is the ribbon's spare, on ground at both ends.

| Column | Odd pin | Net | Even pin | Net |
|---|---|---|---|---|
| 1 | 23 | IO39 | 24 | IO40 |
| 2 | 21 | IO6 | 22 | U0TXD |
| 3 | 19 | IO7 | 20 | PWR_GND |
| 4 | 17 | IO38 | 18 | U0RXD |
| 5 | 15 | DEV_3V3 | 16 | IO2 |
| 6 | 13 | IO37 | 14 | PWR_GND |
| 7 | 11 | IO36 | 12 | IO1 |
| 8 | 9 | IO35 | 10 | IO3 |
| 9 | 7 | IO34 | 8 | PWR_GND |
| 10 | 5 | IO33 | 6 | PWR_GND |
| 11 | 3 | INST_5V_A | 4 | PWR_GND |
| 12 | 1 | INST_5V_A | 2 | INST_5V_A |

## The references

| Reference | BOM row | What it is |
|---|---|---|
| J1 | `J-MCU-C` | the ribbon's carrier end, 2×12 1.27 mm vertical, on the bottom face under the arm, mouth down, key toward the far side |
| J2 | `HDR-MATRIX` | the Matrix's 5V..IO1 pad row, surface mount |
| J3 | `HDR-MATRIX` | the Matrix's IO33..RX pad row, surface mount |
| H1–H3 | `MECH-MX-*` | the hanging mounts: insert in the oak, spacer, the board, washer, screw |

## Revisions

| Rev | Date | What changed | Where |
|---|---|---|---|
| A | 2026-10-03 | First layout, every track by hand (`carrier_routes.py`): a bottom-face bus at 0.7 mm, one ladder of vias onto the top face, 5V, 3V3 and ground on the top face 0.4 mm, PWR_GND poured both faces and stitched. `pcb.py check` passes. Not yet ordered | `matrix-carrier.kicad_pcb`, `layout.yaml`, `carrier_routes.py` |
| B | 2026-10-04 | IO6, the MIDI out's tip line (issue #37), from J-MCU-C pin 2 straight up the bottom face, a via, and into J2.5 on the top face (`carrier_routes.py`). J-MCU-C pin 1 stays unconnected: the bus boxes it in. `pcb.py check` passes | `matrix-carrier.kicad_pcb`, `carrier_routes.py` |
| C | 2026-11-20 | Laid out again by hand on one face (`carrier_layout.py`, which replaces `carrier_routes.py`): the ribbon's pins re-ordered so no line crosses another, every line on the top face, the bottom face one whole ground plane, one via. `pcb.py check` passes; the ribbon check against the main board fails until `J-MCU` follows. Not yet ordered | `matrix-carrier.kicad_sch`, `matrix-carrier.kicad_pcb`, `layout.yaml`, `carrier_layout.py` |
| D | 2026-11-21 | J-MCU-C is a vertical header (owner, 2026-11-21; ADR 0018, *Amendment, 2026-11-21*), its pads where the right-angle header's were, so no track moved. Its outline is not printed (the insulator overhangs the arm's end); its reference and key side are, beside it. `pcb.py check` passes. Not yet ordered | `matrix-carrier.kicad_sch`, `matrix-carrier.kicad_pcb`, `layout.yaml`, `carrier_layout.py` |
| E | 2026-11-22 | J-MCU-C turned half a turn, its key toward the far side: pin *k* is `J-MCU` pin *k*, so the ribbon is a stocked pin-1-to-pin-1 assembly (owner, 2026-11-22; pre-fab review F3; ADR 0018, *Amendment, 2026-11-22*). No pad moved, only the numbers. The spare pin (6) is on ground. The Matrix and its two headers stand further toward the tail by half of what the tail grew (`config/body.yaml` `boards.umb_socket_d`), centred in the longer tail's window (owner, 2026-11-22), so the arm's lines are that much longer. `pcb.py check` passes. Not yet ordered | `matrix-carrier.kicad_sch`, `matrix-carrier.kicad_pcb`, `layout.yaml`, `carrier_layout.py` |
| F | 2026-11-22 | Every line that passes between two of J2's pads stands evenly in the gap, the same room pad to line, line to line and line to pad (owner, 2026-11-21; issue #52 W1); the two service lines step into place by a small 45 degree jog once they are clear of the band. The three necked lines between pads 1 and 2 were already even. `pcb.py check` passes | `carrier_layout.py`, `matrix-carrier.kicad_pcb` |
| G | 2026-11-22 | `IO39` and `IO40` leave J-MCU-C's pins on one 45 degree line from the pad's centre, with no short level piece first (owner, 2026-11-22: a track leaves a pin on a line through its centre; issue #52). |
| H | 2026-11-22 | The lines into `J3` pads 4 and 5 run clear of the pad before they turn, and pad 5's stands under the pad on one 45 and enters it straight (the exit rule in `check_joints`, `docs/reference/tooling.md` §4; owner, 2026-11-22; issue #52). `IO3` still enters `J2` pad 8 on one 45: the near mount's pad and `IO1` leave no room for a straight run, recorded under `joints_exempt:` in `layout.yaml`. |
| I | 2026-11-22 | Fabrication review fixes (issue #57, F5, F6): `J-MCU-C`'s ground pins are relieved by one spoke each (`matrix-carrier.kicad_dru`; ADR 0030, Amendment of 2026-11-22), and the via takes the two-layer recommended ring. `pcb.py check` passes. |
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
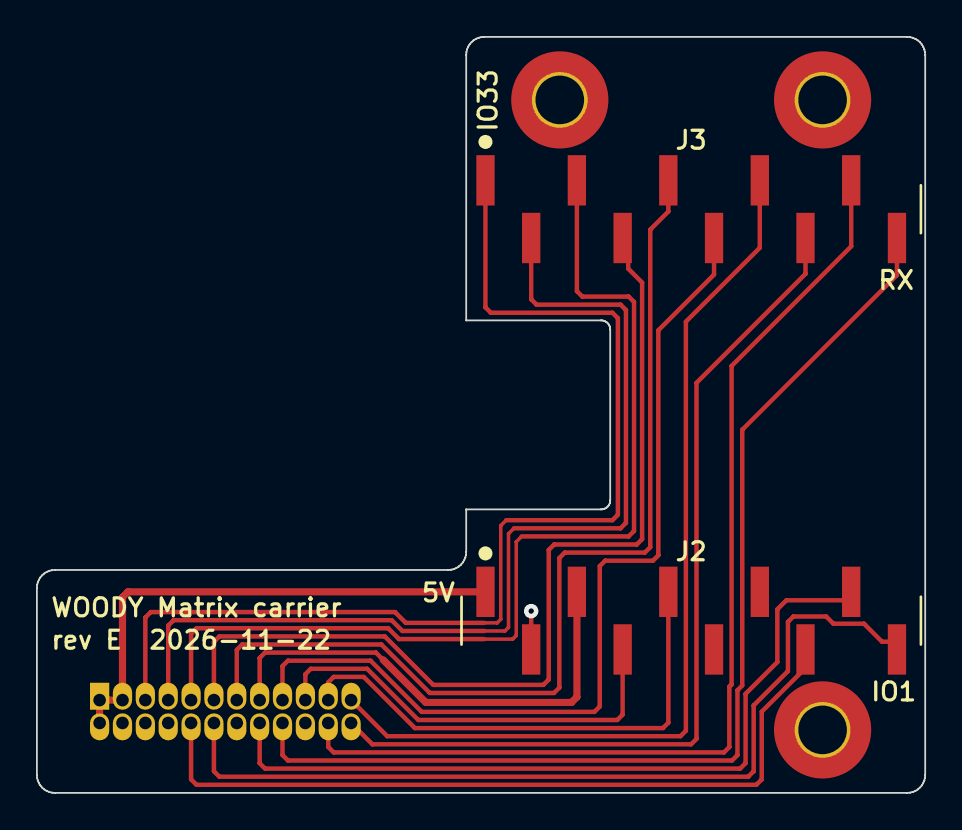
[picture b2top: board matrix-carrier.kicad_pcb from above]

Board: 2 copper layers, 49.3 x 42.0 mm, 6 parts (1 on the bottom side), 18 nets.

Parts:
H1, H2, H3: mount hang; MountingHole_2.7mm_M2.5_Pad_TopBottom
J1: 2x12 1.27mm shrouded box header; IDC-Header_2x12_P1.27mm_Vertical
J2, J3: 1x10 2.54mm pin header, SMD; PinHeader_1x10_P2.54mm_Vertical_SMD_Hanxia_PZ2.54-TP-YQ

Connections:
/DEV_3V3: J1.15, J2.3
/INST_5V_A: J1.1, J1.2, J1.3, J2.1
/IO1: J1.12, J2.10
/IO2: J1.16, J2.9
/IO3: J1.10, J2.8
/IO6: J1.21, J2.5
/IO7: J1.19, J2.4
/IO33: J1.5, J3.1
/IO34: J1.7, J3.2
/IO35: J1.9, J3.3
/IO36: J1.11, J3.4
/IO37: J1.13, J3.5
/IO38: J1.17, J3.6
/IO39: J1.23, J3.7
/IO40: J1.24, J3.8
/U0RXD: J1.18, J3.10
/U0TXD: J1.22, J3.9
PWR_GND: H1.1, H2.1, H3.1, J1.4, J1.6, J1.8, J1.14, J1.20, J2.2

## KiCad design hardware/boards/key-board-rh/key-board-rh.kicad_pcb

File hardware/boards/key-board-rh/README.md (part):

# Right-hand key board — `key-board-rh`

The right hand's six keys (RH1–RH6) and their register. **It is made, checked,
ordered, assembled and brought up exactly as the left-hand board is**, and
[`../key-board-lh/README.md`](../key-board-lh/README.md) is the procedure for
all of it. This page gives only what differs. Where it says nothing, the
left-hand page holds, with `key-board-rh` for `key-board-lh` in every path.

> **Status: orderable as a prototype, not as the instrument's board**, for the
> same reason as the left-hand board. The six switch positions come from
> `config/body.yaml` `layout.rh_gaps` and `layout.rh_offsets` until M2 fills
> `config/key-layout.yaml`, and M3 locks them.

## What differs from the left-hand board

| | Left hand | This board |
|---|---|---|
| Keys | five, LH1–LH5, on inputs H..D | **six**, RH1–RH6, on inputs H..C |
| The register's other inputs | A is a free input with its pull-up (R11, sheet FREE3); B and C are the markers | **no free input**: A and B are the markers (`key-marker-and-bits/allocation.yaml`) |
| The register's decouplers | one, C6, across the ends of pins 16 and 15 | **two, each across a 3V3 pin and the ground pin beside it on the far row**: C7 across pins 11 and 12, C9 across 16 and 15. The two far-row key lines, RH6 and RH5 (pins 13 and 14), leave between them (`rh_layout.py`, *The floorplan*) |
| The register's far-row ground pins | `lh_layout.py` says | pins 12 and 15 each go up through their decoupler's ground pad to a via into the switch-side plane (`rh_layout.py`, *ground*) |
| The register's place | level with LH3, close behind `J-CHAIN` | the same: level with RH3, the left hand's distance behind `J-CHAIN` (owner, 2026-11-20; `rh_layout.py`) |
| The sixth key | none | RH6's line leaves the register's far row, runs along the far edge past RH5 and comes down on the tail side of RH4 |
| The rail's reservoir | C7 | **C8** |
| SER comes from / QH goes to | the main board / the left thumb (`/CHAIN_SER_LH`, `/HOP_LH_LT`) | the left thumb / the right thumb (`/HOP_LT_RH`, `/HOP_RH_RT`), `key-chain-loom.md` |
| Its rail | `V3V3_CHAIN_LH` | `V3V3_CHAIN_RH` |

Everything else is the same, laid out the same way (ADR 0030): every key's
network outside its own switch's pins (`tools/pcb_hand.py`, `KEY_NET`), the
switch-side face one whole ground plane, no pour on the parts face, J1 where
the body CAD puts it, **vertical, its signal row toward the register as the
left hand's is** (ADR 0017, *Amendment, 2026-11-21*), the four corner mounts, the
rules and the board house's limits. `rh_layout.py` is the record of the
layout and rewrites `key-board-rh.kicad_pcb`; no router runs on this board.

## The references

As the left-hand board's table, for six keys:

| Reference | BOM row | What it is |
|---|---|---|
| SW*n*, *n* = 1-6 | `SW1-n` | the switch of key RH*n* |
| R(2*n*-1): R1, R3, … R11 | `R-KEY-SER` | key RH*n*'s series resistor |
| R(2*n*): R2, R4, … R12 | `R-KEY-PU` | key RH*n*'s pull-up |
| C*n*: C1-C6 | `C-KEY` | key RH*n*'s capacitor |
| C7 | `C-DECOUPLE-165` | the register's decoupler |
| C8 | `C-BULK-CHAIN` | the rail's reservoir, beside J1's 3V3 pin |
| U1 | `U-KEYS` | the register, SN74HCS165 |
| J1 | `J-CHAIN` | the key chain's header |
| H1-H4 | (board only) | the corner mounts' holes |
| C9 | `C-DECOUPLE-165` | U1's second decoupler, at VCC (pin 16), review #6-5 |

## Ordering

The left-hand page's *Ordering it — JLCPCB* is the order sheet, with
`key-board-rh` in every file name (`cd hardware/boards/key-board-rh/fab && zip
/tmp/key-board-rh-gerbers.zip *.gbr *.drl *.gbrjob`). It is a **separate design
and a separate order**: one instrument needs one of each. Put both in one cart
so they ship together. It is ordered as the left-hand board is, as **Standard
PCBA on JLC-added rails and fiducials** (owner, 2026-10-04; ADR 0028,
*Amendment, 2026-10-04*): its size (`fab/key-board-rh-job.gbrjob`, `"Size"`) is under
Standard's 70 × 70 mm minimum across. What differs:

- **The gates**: `python3 tools/pcb.py check hardware/boards/key-board-rh`, 0
  errors, and `python3 tools/kicad.py check --board key-board-rh`, PASS - this
  board and the sheets it places, not another board's layout (review #6-3).

- **The parts** (its step 4) are the same six LCSC parts, with the same Basic/Extended split, stock and rotation offsets. This board places R1–R12, C1–C8 and U1: six of each key part, `C-DECOUPLE-165` is C7, and `C-BULK-CHAIN` is C8.
- **The placement preview** (its step 5): C8, not C7, is beside J1's 3V3 pin; and, as there (item 6, review #6-6), JLC's rails and tooling holes land on the rails, clear of the ground pour, the switch pads and the mounting holes, or the order goes with rails outside the outline.
- **The cost** (its step 6), *estimates*:
  - The board is **wider than 100 mm** (its outline, `mechanical/export/key-board-rh.dxf`), so JLC's $2 price for 5 boards up to 100 × 100 mm `[web https://jlcpcb.com/, 2026-10-01]` does not apply. Expect a few dollars more for the bare boards (*estimate* `[from memory]`). The live quote decides.
  - SMT joints: $0.19 [calc: (20 two-pad parts × 2 + U1's 16) = 56 joints × 2 boards × $0.0017].
  - Parts, 2 boards: about $2.65 [calc: per board 6 × 0.0042 + 6 × 0.0046 + 6 × 0.0173 + 0.0189 + 0.0651 + 1.086 = $1.327, at the left-hand page's 2026-10-01 unit prices].
  - Setup, stencil and the one Extended feeder fee are the same as the left-hand board's, and they are charged again: per design, not per cart. The left-hand page's fees are Economic PCBA's, so for this Standard order they are a floor (its step 6).
- **The hand assembly**: buy **six** switches, not five. `J-CHAIN`'s stock (the left-hand page) has to cover both boards.

## Bring-up

As the left-hand board's, with two differences at step 5 (the chain): the
eight bits out, H first, are RH1..RH6 and then the two marker bits, in
`key-marker-and-bits/allocation.yaml`'s order, and there is no free bit.

## Simulation

`sim/`, generated from this board's netlist as the left-hand board's is,
with that board's register model and parameters imported by path, so they
are stated once. At every corner: every key input H..C clears the register's
thresholds open and closed, the high marker (A) reads high, and the draw with
every key closed is six keys' `key-scan-current`.

## Revisions

The letters are design history: the silkscreen and title block read `rev A`
with the latest layout's date until a board is fabricated
(`hardware/boards/main-board/README.md`, *Ordering it*, **Revision**; ADR 0020,
*Amendment 9*).

| Rev | Date | What changed | Where |
|---|---|---|---|
| A | 2026-09-28 | First layout, from the left-hand board's (`layout.yaml`). Not yet ordered; re-laid out 2026-09-29 for the cassette's columns (ADR 0025): the mouth end 0.6 and the tail end 0.2 longer, `J-CHAIN` 13.0 further toward the tail where the shorter ribbon lets the body CAD put it, the register, C7 and C8 following it, the switch side's title moved off the header's tails | git history of this directory |
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
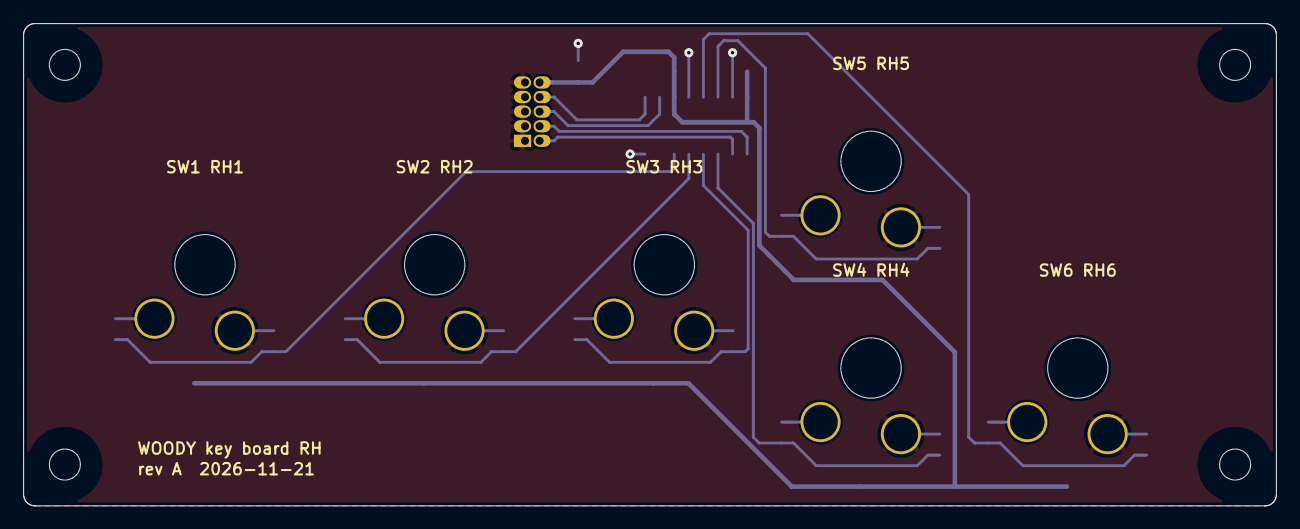
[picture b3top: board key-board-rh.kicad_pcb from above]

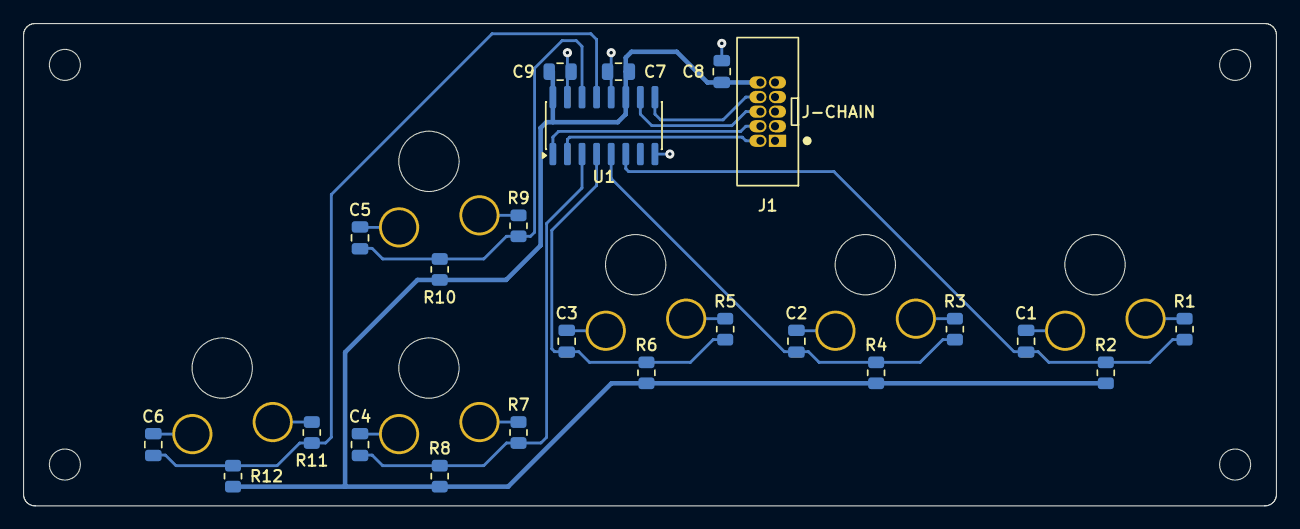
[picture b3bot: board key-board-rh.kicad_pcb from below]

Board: 2 copper layers, 109.1 x 42.0 mm, 33 parts (27 on the bottom side), 18 nets.

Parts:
C1, C2, C3, C4, C5, C6: 47nF; C_0805_2012Metric
C7, C9: 100nF; C_0805_2012Metric
C8: 10uF; C_0805_2012Metric
H1, H2, H3, H4: mount; MountingHole_2.7mm_M2.5
J1: 10-way; IDC-Header_2x05_P1.27mm_CNCTech_3220_Vertical
R1, R3, R5, R7, R9, R11: 100R 1%; R_0805_2012Metric
R2, R4, R6, R8, R10, R12: 2k2 1%; R_0805_2012Metric
SW1, SW2, SW3, SW4, SW5, SW6: KS-33; SW_Gateron_KS33_1u
U1: 74HCS165; SOIC-16_3.9x9.9mm_P1.27mm

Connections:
/CHAIN_SCK: J1.2, U1.2
/CHAIN_SHLD: J1.4, U1.1
/HOP_LT_RH: J1.6, U1.10
/HOP_RH_RT: J1.8, U1.9
/KEY_RH1: C1.1, R1.1, R2.2, U1.6
/KEY_RH2: C2.1, R3.1, R4.2, U1.5
/KEY_RH3: C3.1, R5.1, R6.2, U1.4
/KEY_RH4: C4.1, R7.1, R8.2, U1.3
/KEY_RH5: C5.1, R9.1, R10.2, U1.14
/KEY_RH6: C6.1, R11.1, R12.2, U1.13
/RH1/SWITCH_LEG: R1.2, SW1.1
/RH2/SWITCH_LEG: R3.2, SW2.1
/RH3/SWITCH_LEG: R5.2, SW3.1
/RH4/SWITCH_LEG: R7.2, SW4.1
/RH5/SWITCH_LEG: R9.2, SW5.1
/RH6/SWITCH_LEG: R11.2, SW6.1
GND_CHAIN: C1.2, C2.2, C3.2, C4.2, C5.2, C6.2, C7.2, C8.2, C9.2, J1.1, J1.3, J1.5, J1.7, J1.9, SW1.2, SW2.2, SW3.2, SW4.2, SW5.2, SW6.2, U1.8, U1.12, U1.15
V3V3_CHAIN_RH: C7.1, C8.1, C9.1, J1.10, R2.1, R4.1, R6.1, R8.1, R10.1, R12.1, U1.11, U1.16

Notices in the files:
hardware/boards/main-board/README.md:
all rev A"; ADR 0020, *Amendment 9*); the key boards' pages cite this paragraph. `pcb.py check` fails a board whose title block or silkscreen has lost either (`check_title`, #33).
